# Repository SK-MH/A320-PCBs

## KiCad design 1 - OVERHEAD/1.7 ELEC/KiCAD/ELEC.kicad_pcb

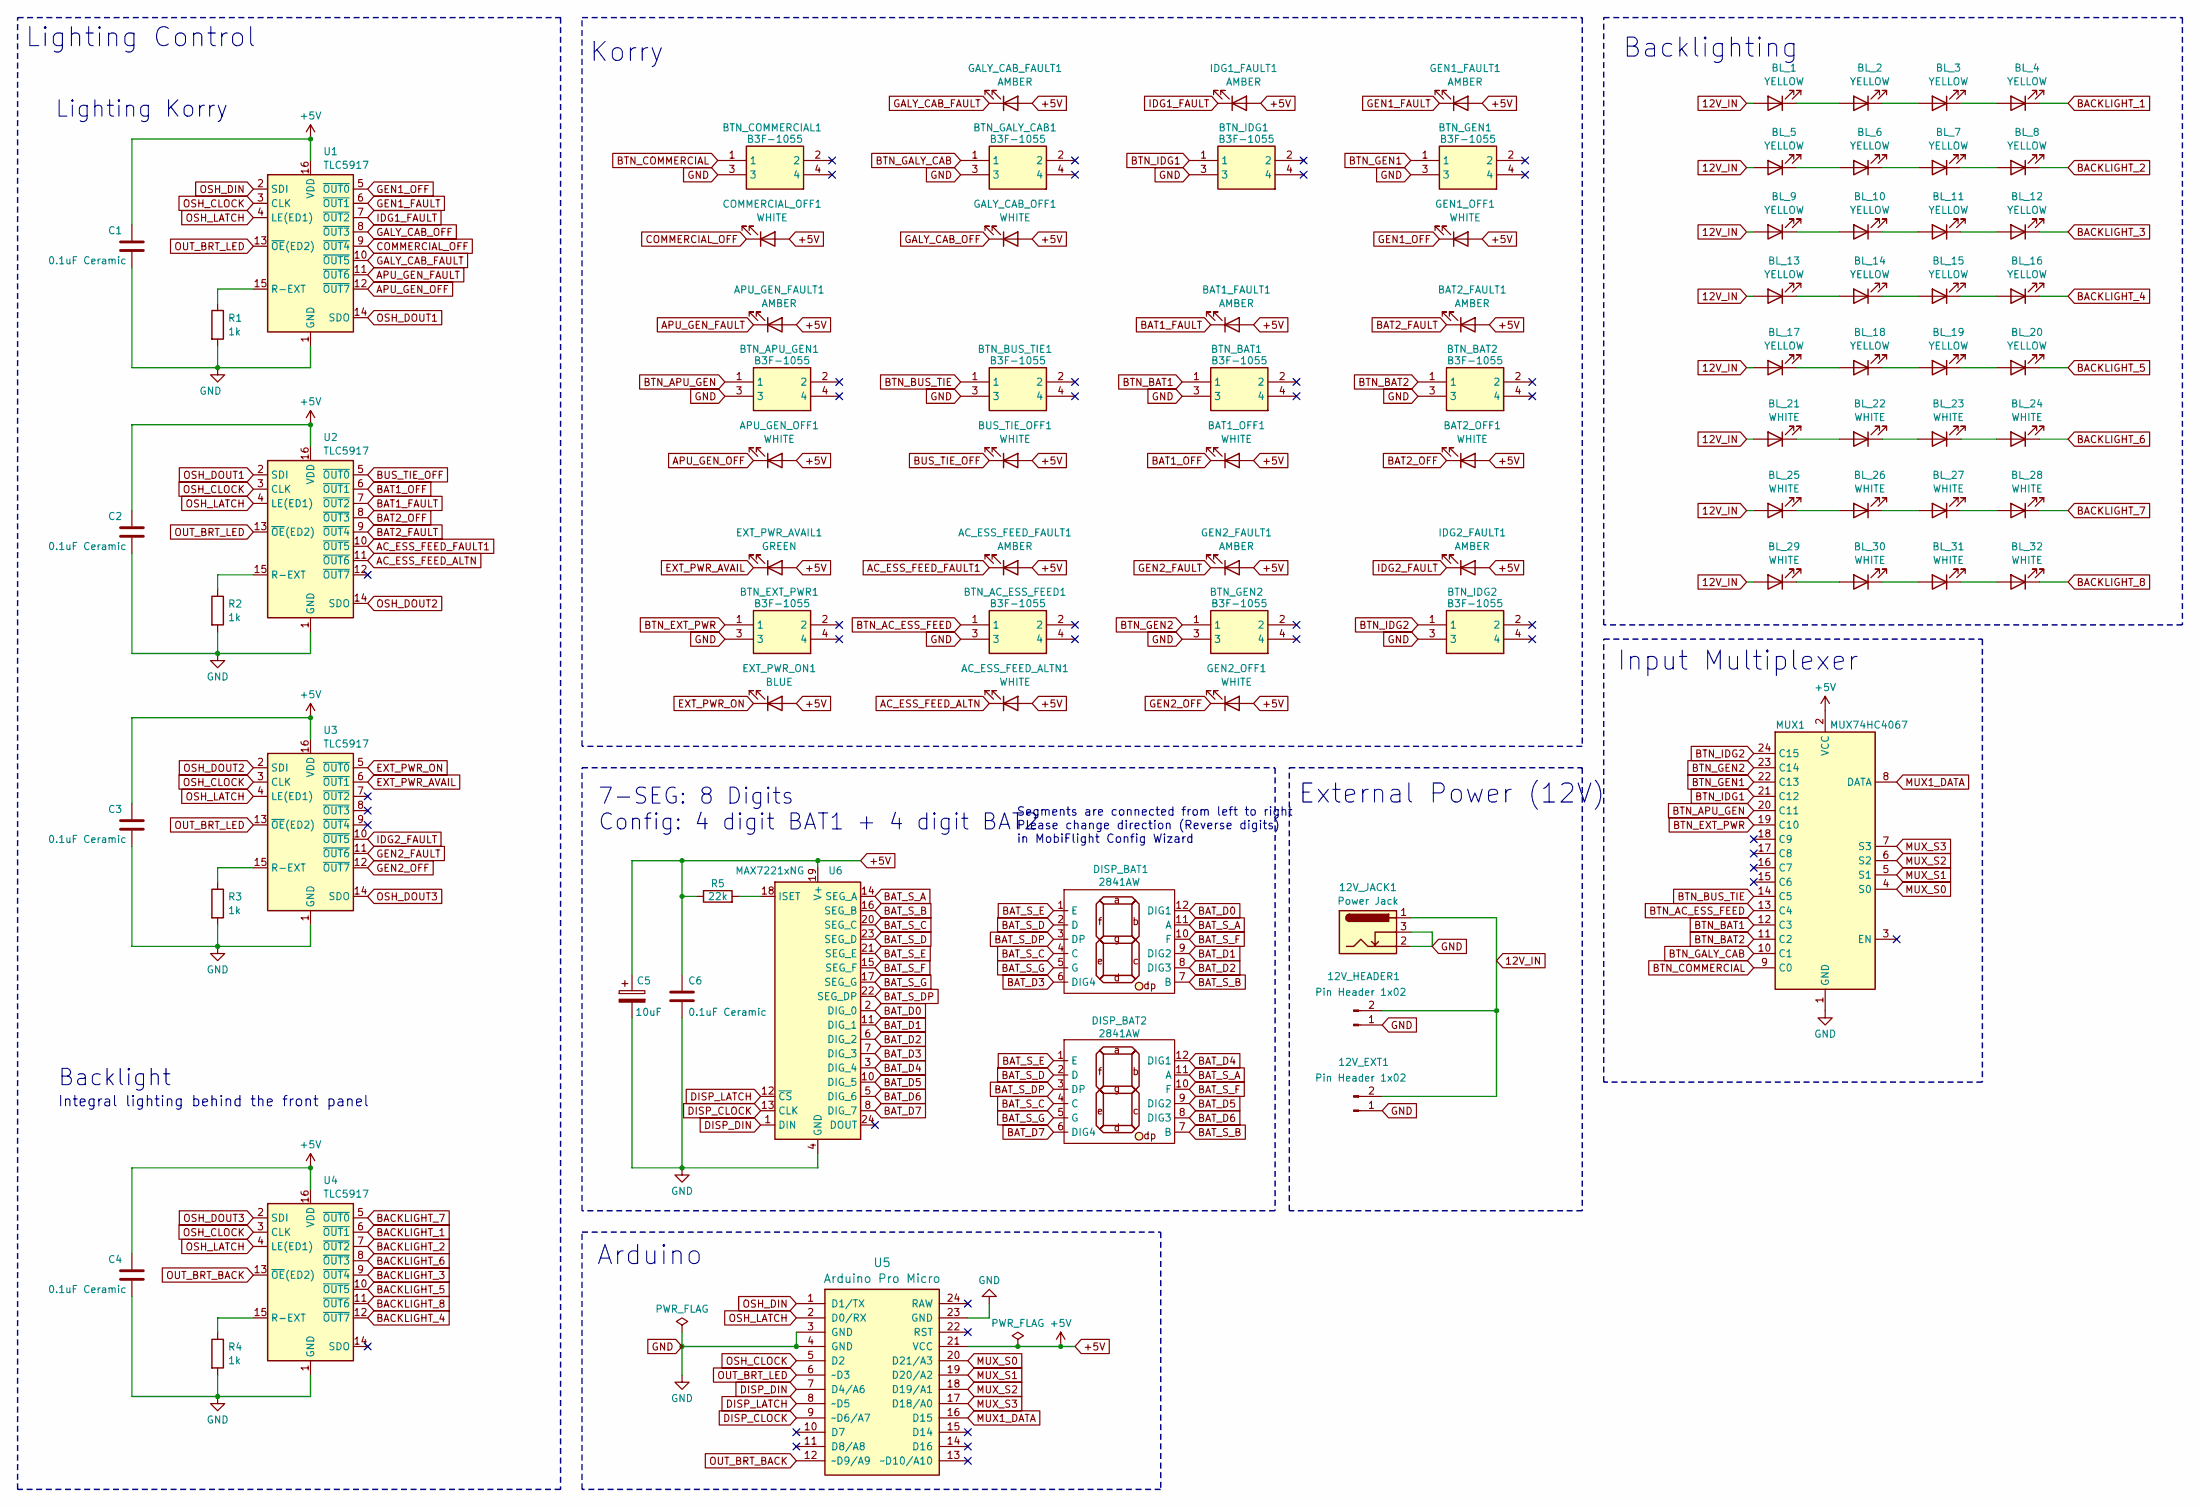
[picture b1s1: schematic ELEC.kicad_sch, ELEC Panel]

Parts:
12V_EXT1, 12V_HEADER1: Pin Header 1x02; JST_EH_B2B-EH-A_1x02_P2.50mm_Vertical
12V_JACK1: Power Jack; BarrelJack_Horizontal
AC_ESS_FEED_ALTN1: WHITE; LED_D3.0mm
AC_ESS_FEED_FAULT1: AMBER; LED_D3.0mm
APU_GEN_FAULT1: AMBER; LED_D3.0mm
APU_GEN_OFF1: WHITE; LED_D3.0mm
BAT1_FAULT1, BAT2_FAULT1: AMBER; LED_D3.0mm
BAT1_OFF1, BAT2_OFF1: WHITE; LED_D3.0mm
BL_1, BL_2, BL_3, BL_4, BL_5, BL_6, BL_7, BL_8, BL_9, BL_10, BL_11, BL_12, BL_13, BL_14, BL_15, BL_16, BL_17, BL_18, BL_19, BL_20: YELLOW; LED_D3.0mm
BL_21, BL_22, BL_23, BL_24, BL_25, BL_26, BL_27, BL_28, BL_29, BL_30, BL_31, BL_32: WHITE; LED_D3.0mm
BTN_AC_ESS_FEED1: B3F-1055; B3F1000; Mouser Part Number 653-B3F-1055
BTN_APU_GEN1: B3F-1055; B3F1000; Mouser Part Number 653-B3F-1055
BTN_BAT1, BTN_BAT2: B3F-1055; B3F1000; Mouser Part Number 653-B3F-1055
BTN_BUS_TIE1: B3F-1055; B3F1000; Mouser Part Number 653-B3F-1055
BTN_COMMERCIAL1: B3F-1055; B3F1000; Mouser Part Number 653-B3F-1055
BTN_EXT_PWR1: B3F-1055; B3F1000; Mouser Part Number 653-B3F-1055
BTN_GALY_CAB1: B3F-1055; B3F1000; Mouser Part Number 653-B3F-1055
BTN_GEN1, BTN_GEN2: B3F-1055; B3F1000; Mouser Part Number 653-B3F-1055
BTN_IDG1, BTN_IDG2: B3F-1055; B3F1000; Mouser Part Number 653-B3F-1055
BUS_TIE_OFF1: WHITE; LED_D3.0mm
C1, C2, C3, C4, C6: 0.1uF Ceramic; C_Disc_D3.0mm_W1.6mm_P2.50mm
C5: 10uF; CP_Radial_D4.0mm_P1.50mm
COMMERCIAL_OFF1: WHITE; LED_D3.0mm
DISP_BAT1, DISP_BAT2: 2841AW
EXT_PWR_AVAIL1: GREEN; LED_D3.0mm
EXT_PWR_ON1: BLUE; LED_D3.0mm
GALY_CAB_FAULT1: AMBER; LED_D3.0mm
GALY_CAB_OFF1: WHITE; LED_D3.0mm
GEN1_FAULT1, GEN2_FAULT1: AMBER; LED_D3.0mm
GEN1_OFF1, GEN2_OFF1: WHITE; LED_D3.0mm
IDG1_FAULT1, IDG2_FAULT1: AMBER; LED_D3.0mm
MUX1: MUX74HC4067
R1, R2, R3, R4: 1k; R_Axial_DIN0204_L3.6mm_D1.6mm_P7.62mm_Horizontal
R5: 22k; R_Axial_DIN0204_L3.6mm_D1.6mm_P7.62mm_Horizontal
U1, U2, U3, U4: TLC5917; DIP-16_W7.62mm
U5: Arduino Pro Micro; Sparkfun_Pro_Micro
U6: MAX7221xNG; DIP-24_W7.62mm

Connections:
12V_IN: 12V_EXT1.2, 12V_HEADER1.2, 12V_JACK1.1, BL_1.2 (A), BL_5.2 (A), BL_9.2 (A), BL_13.2 (A), BL_17.2 (A), BL_21.2 (A), BL_25.2 (A), BL_29.2 (A)
+5V: AC_ESS_FEED_ALTN1.2 (A), AC_ESS_FEED_FAULT1.2 (A), APU_GEN_FAULT1.2 (A), APU_GEN_OFF1.2 (A), BAT1_FAULT1.2 (A), BAT1_OFF1.2 (A), BAT2_FAULT1.2 (A), BAT2_OFF1.2 (A), BUS_TIE_OFF1.2 (A), C1.1, C2.1, C3.1, C4.1, C5.1, C6.1, COMMERCIAL_OFF1.2 (A), EXT_PWR_AVAIL1.2 (A), EXT_PWR_ON1.2 (A), GALY_CAB_FAULT1.2 (A), GALY_CAB_OFF1.2 (A), GEN1_FAULT1.2 (A), GEN1_OFF1.2 (A), GEN2_FAULT1.2 (A), GEN2_OFF1.2 (A), IDG1_FAULT1.2 (A), IDG2_FAULT1.2 (A), MUX1.2 (VCC), R5.1, U1.16 (VDD), U2.16 (VDD), U3.16 (VDD), U4.16 (VDD), U5.21 (VCC), U6.19 (V+)
AC_ESS_FEED_ALTN: AC_ESS_FEED_ALTN1.1 (K), U2.11 (~OUT6)
AC_ESS_FEED_FAULT1: AC_ESS_FEED_FAULT1.1 (K), U2.10 (~OUT5)
APU_GEN_FAULT: APU_GEN_FAULT1.1 (K), U1.11 (~OUT6)
APU_GEN_OFF: APU_GEN_OFF1.1 (K), U1.12 (~OUT7)
BACKLIGHT_1: BL_4.1 (K), U4.6 (~OUT1)
BACKLIGHT_2: BL_8.1 (K), U4.7 (~OUT2)
BACKLIGHT_3: BL_12.1 (K), U4.9 (~OUT4)
BACKLIGHT_4: BL_16.1 (K), U4.12 (~OUT7)
BACKLIGHT_5: BL_20.1 (K), U4.10 (~OUT5)
BACKLIGHT_6: BL_24.1 (K), U4.8 (~OUT3)
BACKLIGHT_7: BL_28.1 (K), U4.5 (~OUT0)
BACKLIGHT_8: BL_32.1 (K), U4.11 (~OUT6)
BAT1_FAULT: BAT1_FAULT1.1 (K), U2.7 (~OUT2)
BAT1_OFF: BAT1_OFF1.1 (K), U2.6 (~OUT1)
BAT2_FAULT: BAT2_FAULT1.1 (K), U2.9 (~OUT4)
BAT2_OFF: BAT2_OFF1.1 (K), U2.8 (~OUT3)
BAT_D0: DISP_BAT1.12 (DIG1), U6.2 (DIG_0)
BAT_D1: DISP_BAT1.9 (DIG2), U6.11 (DIG_1)
BAT_D2: DISP_BAT1.8 (DIG3), U6.6 (DIG_2)
BAT_D3: DISP_BAT1.6 (DIG4), U6.7 (DIG_3)
BAT_D4: DISP_BAT2.12 (DIG1), U6.3 (DIG_4)
BAT_D5: DISP_BAT2.9 (DIG2), U6.10 (DIG_5)
BAT_D6: DISP_BAT2.8 (DIG3), U6.5 (DIG_6)
BAT_D7: DISP_BAT2.6 (DIG4), U6.8 (DIG_7)
BAT_S_A: DISP_BAT1.11 (A), DISP_BAT2.11 (A), U6.14 (SEG_A)
BAT_S_B: DISP_BAT1.7 (B), DISP_BAT2.7 (B), U6.16 (SEG_B)
BAT_S_C: DISP_BAT1.4 (C), DISP_BAT2.4 (C), U6.20 (SEG_C)
BAT_S_D: DISP_BAT1.2 (D), DISP_BAT2.2 (D), U6.23 (SEG_D)
BAT_S_DP: DISP_BAT1.3 (DP), DISP_BAT2.3 (DP), U6.22 (SEG_DP)
BAT_S_E: DISP_BAT1.1 (E), DISP_BAT2.1 (E), U6.21 (SEG_E)
BAT_S_F: DISP_BAT1.10 (F), DISP_BAT2.10 (F), U6.15 (SEG_F)
BAT_S_G: DISP_BAT1.5 (G), DISP_BAT2.5 (G), U6.17 (SEG_G)
BTN_AC_ESS_FEED: BTN_AC_ESS_FEED1.1, MUX1.13 (C4)
BTN_APU_GEN: BTN_APU_GEN1.1, MUX1.20 (C11)
BTN_BAT1: BTN_BAT1.1, MUX1.12 (C3)
BTN_BAT2: BTN_BAT2.1, MUX1.11 (C2)
BTN_BUS_TIE: BTN_BUS_TIE1.1, MUX1.14 (C5)
BTN_COMMERCIAL: BTN_COMMERCIAL1.1, MUX1.9 (C0)
BTN_EXT_PWR: BTN_EXT_PWR1.1, MUX1.19 (C10)
BTN_GALY_CAB: BTN_GALY_CAB1.1, MUX1.10 (C1)
BTN_GEN1: BTN_GEN1.1, MUX1.22 (C13)
BTN_GEN2: BTN_GEN2.1, MUX1.23 (C14)
BTN_IDG1: BTN_IDG1.1, MUX1.21 (C12)
BTN_IDG2: BTN_IDG2.1, MUX1.24 (C15)
BUS_TIE_OFF: BUS_TIE_OFF1.1 (K), U2.5 (~OUT0)
COMMERCIAL_OFF: COMMERCIAL_OFF1.1 (K), U1.9 (~OUT4)
DISP_CLOCK: U5.9 (~D6/A7), U6.13 (CLK)
DISP_DIN: U5.7 (D4/A6), U6.1 (DIN)
DISP_LATCH: U5.8 (~D5), U6.12 (~CS)
EXT_PWR_AVAIL: EXT_PWR_AVAIL1.1 (K), U3.6 (~OUT1)
EXT_PWR_ON: EXT_PWR_ON1.1 (K), U3.5 (~OUT0)
GALY_CAB_FAULT: GALY_CAB_FAULT1.1 (K), U1.10 (~OUT5)
GALY_CAB_OFF: GALY_CAB_OFF1.1 (K), U1.8 (~OUT3)
GEN1_FAULT: GEN1_FAULT1.1 (K), U1.6 (~OUT1)
GEN1_OFF: GEN1_OFF1.1 (K), U1.5 (~OUT0)
GEN2_FAULT: GEN2_FAULT1.1 (K), U3.11 (~OUT6)
GEN2_OFF: GEN2_OFF1.1 (K), U3.12 (~OUT7)
GND: 12V_EXT1.1, 12V_HEADER1.1, 12V_JACK1.2, 12V_JACK1.3, BTN_AC_ESS_FEED1.3, BTN_APU_GEN1.3, BTN_BAT1.3, BTN_BAT2.3, BTN_BUS_TIE1.3, BTN_COMMERCIAL1.3, BTN_EXT_PWR1.3, BTN_GALY_CAB1.3, BTN_GEN1.3, BTN_GEN2.3, BTN_IDG1.3, BTN_IDG2.3, C1.2, C2.2, C3.2, C4.2, C5.2, C6.2, MUX1.1 (GND), R1.2, R2.2, R3.2, R4.2, U1.1 (GND), U2.1 (GND), U3.1 (GND), U4.1 (GND), U5.3 (GND), U5.4 (GND), U5.23 (GND), U6.4 (GND), U6.9 (GND)
IDG1_FAULT: IDG1_FAULT1.1 (K), U1.7 (~OUT2)
IDG2_FAULT: IDG2_FAULT1.1 (K), U3.10 (~OUT5)
MUX1_DATA: MUX1.8 (DATA), U5.16 (D15)
MUX_S0: MUX1.4 (S0), U5.20 (D21/A3)
MUX_S1: MUX1.5 (S1), U5.19 (D20/A2)
MUX_S2: MUX1.6 (S2), U5.18 (D19/A1)
MUX_S3: MUX1.7 (S3), U5.17 (D18/A0)
unnamed: BL_1.1 (K), BL_2.2 (A)
unnamed: BL_2.1 (K), BL_3.2 (A)
unnamed: BL_3.1 (K), BL_4.2 (A)
unnamed: BL_5.1 (K), BL_6.2 (A)
unnamed: BL_6.1 (K), BL_7.2 (A)
unnamed: BL_7.1 (K), BL_8.2 (A)
unnamed: BL_9.1 (K), BL_10.2 (A)
unnamed: BL_10.1 (K), BL_11.2 (A)
unnamed: BL_11.1 (K), BL_12.2 (A)
unnamed: BL_13.1 (K), BL_14.2 (A)
unnamed: BL_14.1 (K), BL_15.2 (A)
unnamed: BL_15.1 (K), BL_16.2 (A)
unnamed: BL_17.1 (K), BL_18.2 (A)
unnamed: BL_18.1 (K), BL_19.2 (A)
unnamed: BL_19.1 (K), BL_20.2 (A)
unnamed: BL_21.1 (K), BL_22.2 (A)
unnamed: BL_22.1 (K), BL_23.2 (A)
unnamed: BL_23.1 (K), BL_24.2 (A)
unnamed: BL_25.1 (K), BL_26.2 (A)
unnamed: BL_26.1 (K), BL_27.2 (A)
unnamed: BL_27.1 (K), BL_28.2 (A)
unnamed: BL_29.1 (K), BL_30.2 (A)
unnamed: BL_30.1 (K), BL_31.2 (A)
unnamed: BL_31.1 (K), BL_32.2 (A)
unnamed: R1.1, U1.15 (R-EXT)
unnamed: R2.1, U2.15 (R-EXT)
unnamed: R3.1, U3.15 (R-EXT)
unnamed: R4.1, U4.15 (R-EXT)
unnamed: R5.2, U6.18 (ISET)
OSH_CLOCK: U1.3 (CLK), U2.3 (CLK), U3.3 (CLK), U4.3 (CLK), U5.5 (D2)
OSH_DIN: U1.2 (SDI), U5.1 (D1/TX)
OSH_DOUT1: U1.14 (SDO), U2.2 (SDI)
OSH_DOUT2: U2.14 (SDO), U3.2 (SDI)
OSH_DOUT3: U3.14 (SDO), U4.2 (SDI)
OSH_LATCH: U1.4 (LE(ED1)), U2.4 (LE(ED1)), U3.4 (LE(ED1)), U4.4 (LE(ED1)), U5.2 (D0/RX)
OUT_BRT_BACK: U4.13 (~OE(ED2)), U5.12 (~D9/A9)
OUT_BRT_LED: U1.13 (~OE(ED2)), U2.13 (~OE(ED2)), U3.13 (~OE(ED2)), U5.6 (~D3)

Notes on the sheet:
Backlighting
7-SEG: 8 Digits Config: 4 digit BAT1 + 4 digit BAT2
Arduino
Korry
Segments are connected from left to right Please change direction (Reverse digits) in MobiFlight Config Wizard
Input Multiplexer
External Power (12V)
Lighting Korry
Lighting Control
Integral lighting behind the front panel
Backlight

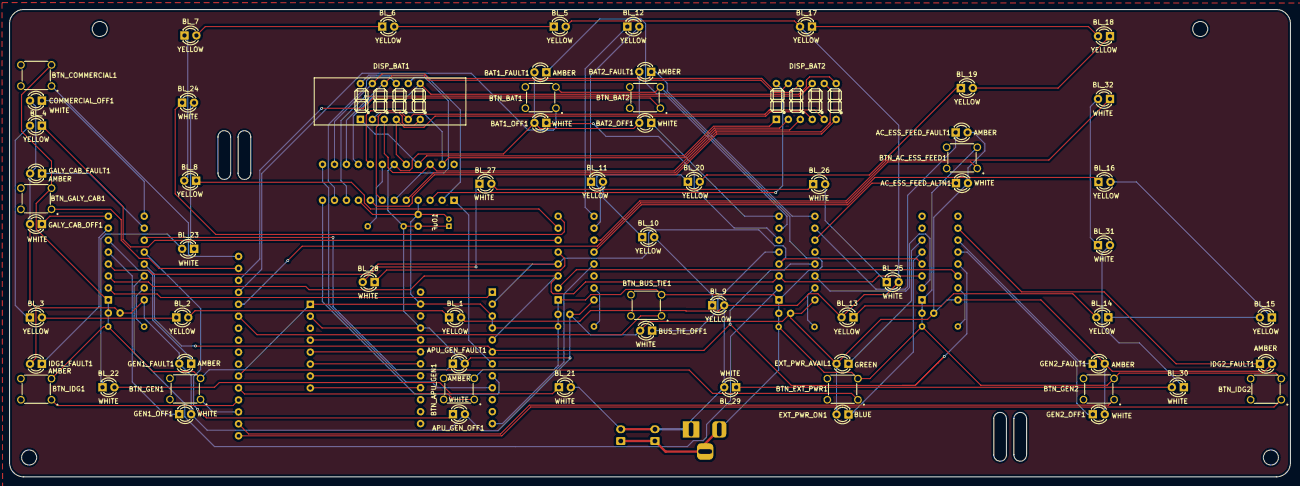
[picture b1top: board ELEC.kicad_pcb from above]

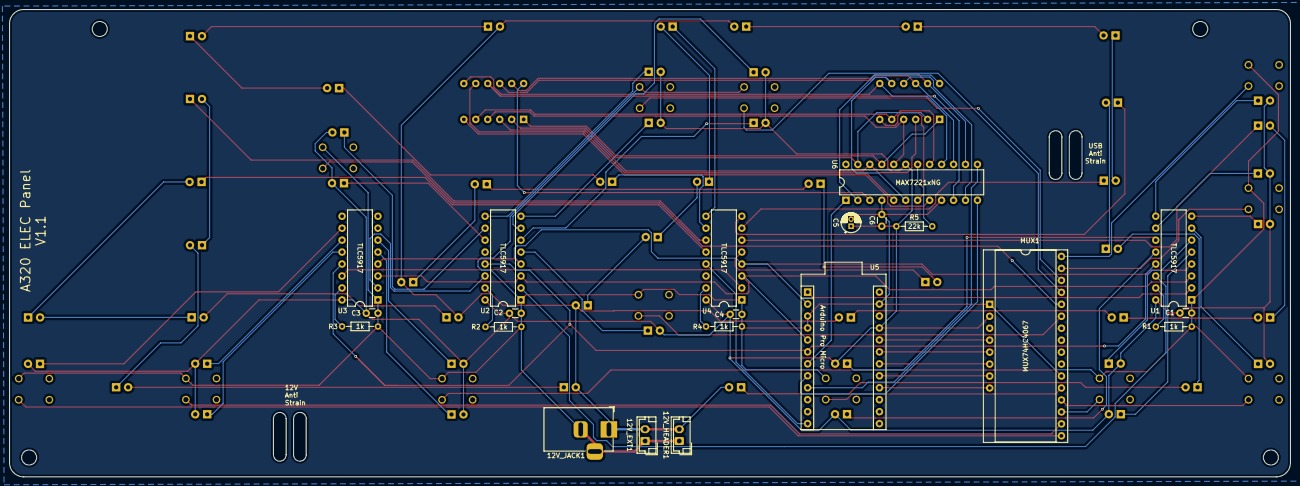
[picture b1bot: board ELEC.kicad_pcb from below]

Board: 2 copper layers, 272.1 x 99.3 mm, 87 parts (21 on the bottom side), 104 nets.

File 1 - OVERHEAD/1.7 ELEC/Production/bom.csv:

Designator,Footprint,Quantity,Value,LCSC Part #
"12V_EXT1, 12V_HEADER1",JST_EH_B2B-EH-A_1x02_P2.50mm_Vertical,2,Pin Header 1x02,
12V_JACK1,BarrelJack_Horizontal,1,Power Jack,
"AC_ESS_FEED_ALTN1, APU_GEN_OFF1, BAT1_OFF1, BAT2_OFF1, BL_21, BL_22, BL_23, BL_24, BL_25, BL_26, BL_27, BL_28, BL_29, BL_30, BL_31, BL_32, BUS_TIE_OFF1, COMMERCIAL_OFF1, GALY_CAB_OFF1, GEN1_OFF1, GEN2_OFF1",LED_D3.0mm,21,WHITE,
"AC_ESS_FEED_FAULT1, APU_GEN_FAULT1, BAT1_FAULT1, BAT2_FAULT1, GALY_CAB_FAULT1, GEN1_FAULT1, GEN2_FAULT1, IDG1_FAULT1, IDG2_FAULT1",LED_D3.0mm,9,AMBER,
"BL_1, BL_10, BL_11, BL_12, BL_13, BL_14, BL_15, BL_16, BL_17, BL_18, BL_19, BL_2, BL_20, BL_3, BL_4, BL_5, BL_6, BL_7, BL_8, BL_9",LED_D3.0mm,20,YELLOW,
"BTN_AC_ESS_FEED1, BTN_APU_GEN1, BTN_BAT1, BTN_BAT2, BTN_BUS_TIE1, BTN_COMMERCIAL1, BTN_EXT_PWR1, BTN_GALY_CAB1, BTN_GEN1, BTN_GEN2, BTN_IDG1, BTN_IDG2",B3F1000,12,B3F-1055,
"C1, C2, C3, C4, C6",C_Disc_D3.0mm_W1.6mm_P2.50mm,5,0.1uF Ceramic,
C5,CP_Radial_D4.0mm_P1.50mm,1,10uF,
"DISP_BAT1, DISP_BAT2",2841AW,2,2841AW,
EXT_PWR_AVAIL1,LED_D3.0mm,1,GREEN,
EXT_PWR_ON1,LED_D3.0mm,1,BLUE,
MUX1,MUX74HC4067,1,MUX74HC4067,
"R1, R2, R3, R4",R_Axial_DIN0204_L3.6mm_D1.6mm_P7.62mm_Horizontal,4,1k,
R5,R_Axial_DIN0204_L3.6mm_D1.6mm_P7.62mm_Horizontal,1,22k,
"U1, U2, U3, U4",DIP-16_W7.62mm,4,TLC5917,
U5,Sparkfun_Pro_Micro,1,Arduino Pro Micro,
U6,DIP-24_W7.62mm,1,MAX7221xNG,

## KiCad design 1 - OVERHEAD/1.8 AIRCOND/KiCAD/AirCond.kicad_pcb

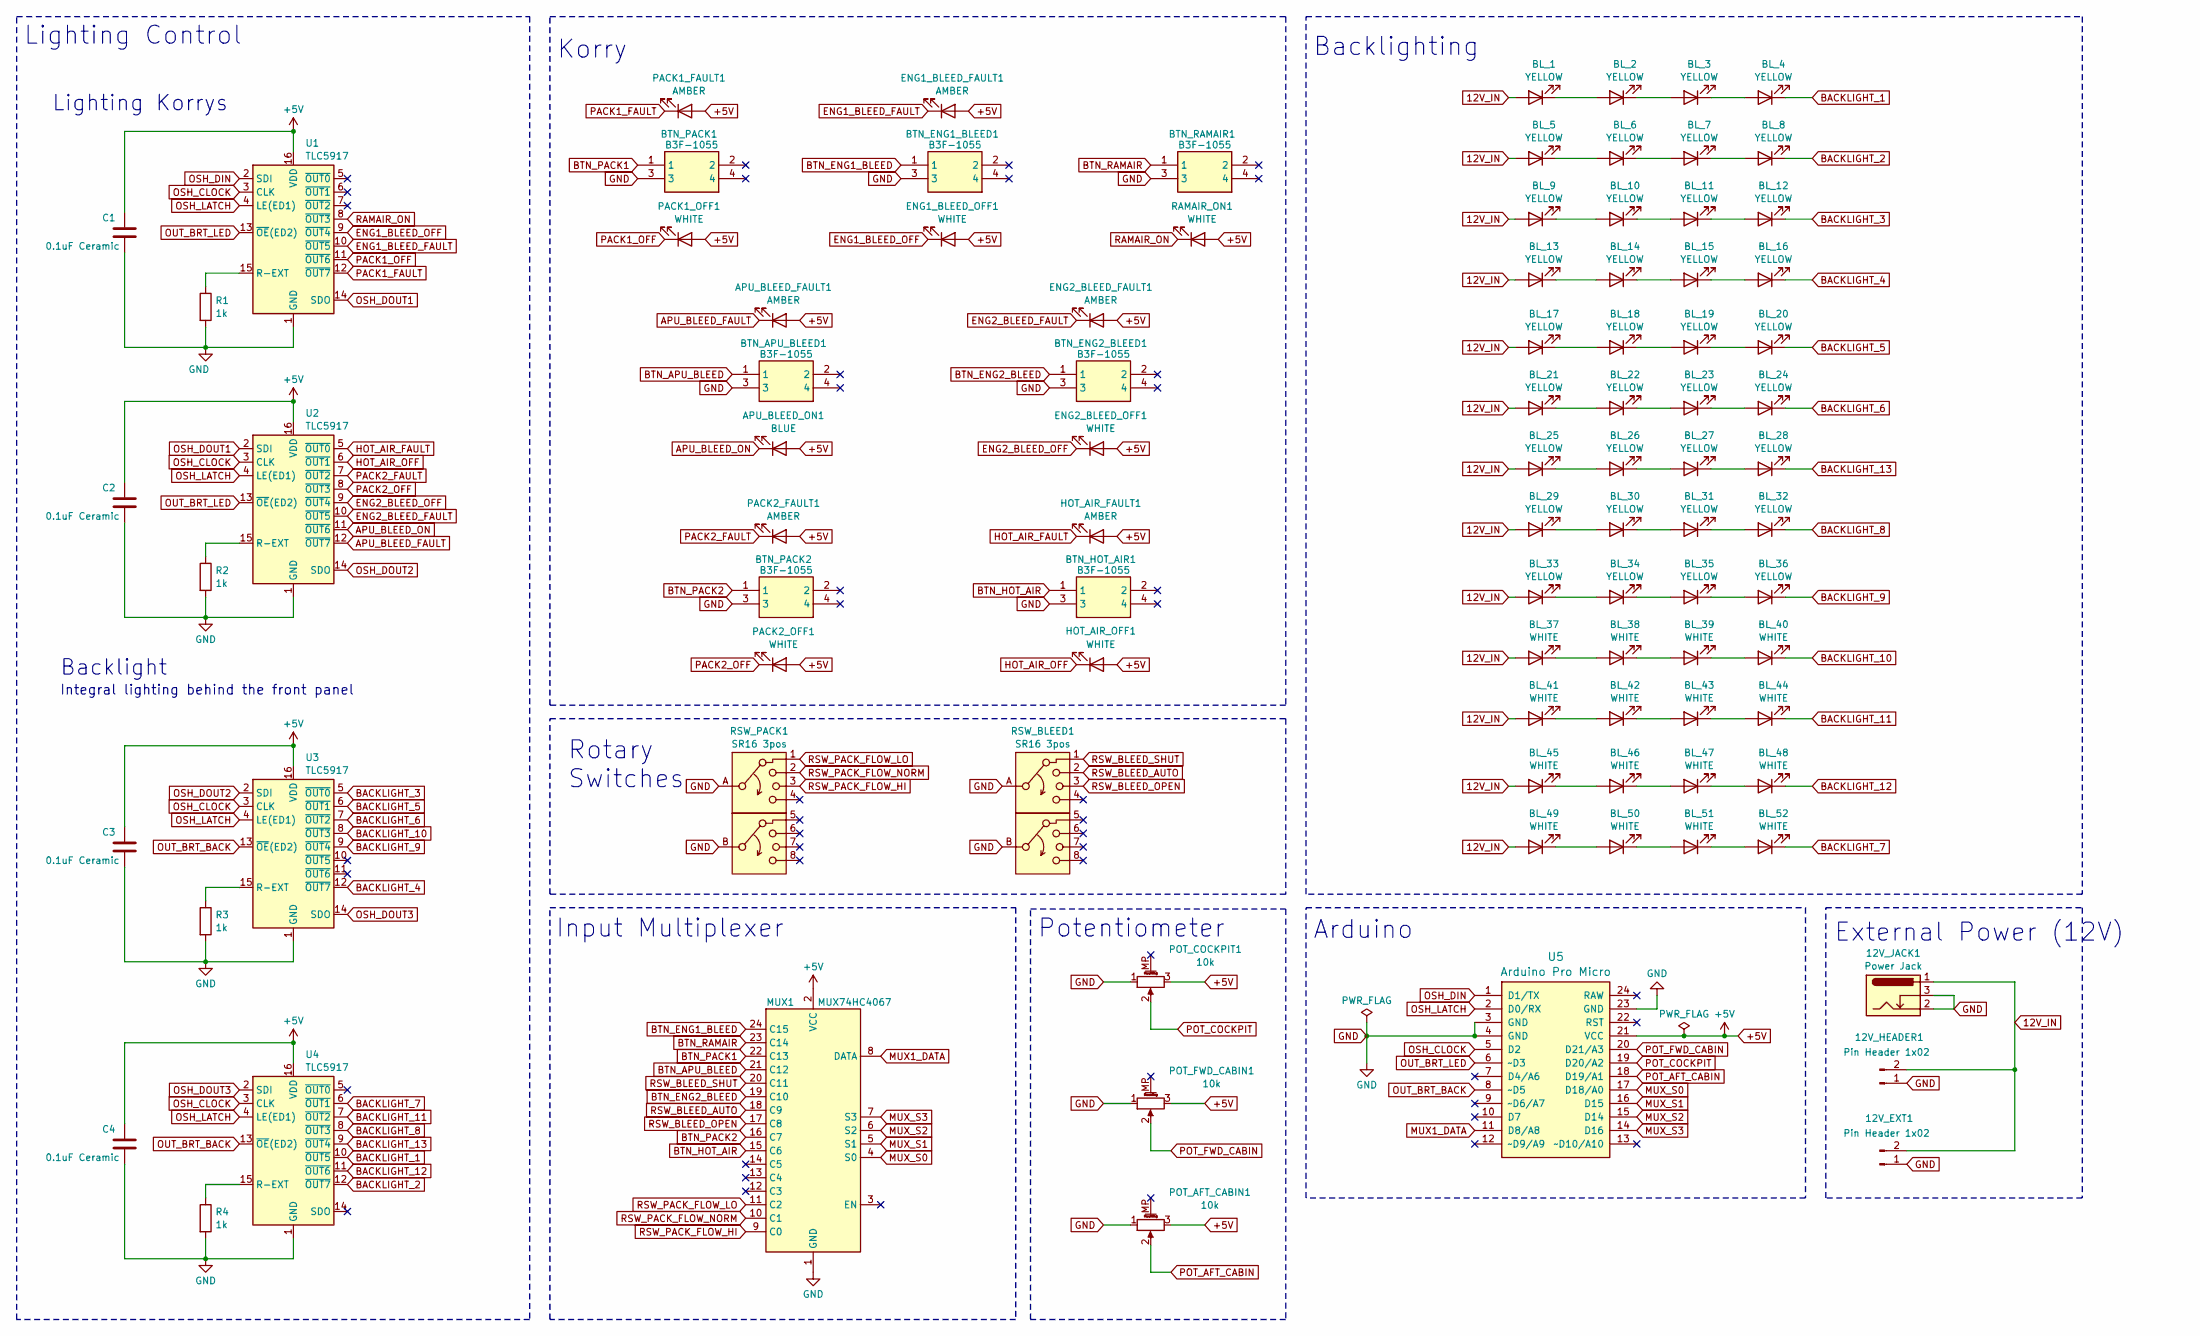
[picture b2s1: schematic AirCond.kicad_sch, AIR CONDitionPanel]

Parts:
12V_EXT1, 12V_HEADER1: Pin Header 1x02; JST_EH_B2B-EH-A_1x02_P2.50mm_Vertical
12V_JACK1: Power Jack; BarrelJack_Horizontal
APU_BLEED_FAULT1: AMBER; LED_D3.0mm
APU_BLEED_ON1: BLUE; LED_D3.0mm
BL_1, BL_2, BL_3, BL_4, BL_5, BL_6, BL_7, BL_8, BL_9, BL_10, BL_11, BL_12, BL_13, BL_14, BL_15, BL_16, BL_17, BL_18, BL_19, BL_20, BL_21, BL_22, BL_23, BL_24, BL_25, BL_26, BL_27, BL_28, BL_29, BL_30, BL_31, BL_32, BL_33, BL_34, BL_35, BL_36: YELLOW; LED_D3.0mm
BL_37, BL_38, BL_39, BL_40, BL_41, BL_42, BL_43, BL_44, BL_45, BL_46, BL_47, BL_48, BL_49, BL_50, BL_51, BL_52: WHITE; LED_D3.0mm
BTN_APU_BLEED1: B3F-1055; B3F1000; Mouser Part Number 653-B3F-1055
BTN_ENG1_BLEED1, BTN_ENG2_BLEED1: B3F-1055; B3F1000; Mouser Part Number 653-B3F-1055
BTN_HOT_AIR1: B3F-1055; B3F1000; Mouser Part Number 653-B3F-1055
BTN_PACK1, BTN_PACK2: B3F-1055; B3F1000; Mouser Part Number 653-B3F-1055
BTN_RAMAIR1: B3F-1055; B3F1000; Mouser Part Number 653-B3F-1055
C1, C2, C3, C4: 0.1uF Ceramic; C_Disc_D3.0mm_W1.6mm_P2.50mm
ENG1_BLEED_FAULT1, ENG2_BLEED_FAULT1: AMBER; LED_D3.0mm
ENG1_BLEED_OFF1, ENG2_BLEED_OFF1: WHITE; LED_D3.0mm
HOT_AIR_FAULT1: AMBER; LED_D3.0mm
HOT_AIR_OFF1: WHITE; LED_D3.0mm
MUX1: MUX74HC4067
PACK1_FAULT1, PACK2_FAULT1: AMBER; LED_D3.0mm
PACK1_OFF1, PACK2_OFF1: WHITE; LED_D3.0mm
POT_AFT_CABIN1: 10k; Potentiometer_Alps_RK09K_Single_Vertical
POT_COCKPIT1: 10k; Potentiometer_Alps_RK09K_Single_Vertical
POT_FWD_CABIN1: 10k; Potentiometer_Alps_RK09K_Single_Vertical
R1, R2, R3, R4: 1k; R_Axial_DIN0204_L3.6mm_D1.6mm_P7.62mm_Horizontal
RAMAIR_ON1: WHITE; LED_D3.0mm
RSW_BLEED1: SR16 3pos; SR16-AB
RSW_PACK1: SR16 3pos; SR16-AB
U1, U2, U3, U4: TLC5917; DIP-16_W7.62mm
U5: Arduino Pro Micro; Sparkfun_Pro_Micro

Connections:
12V_IN: 12V_EXT1.2, 12V_HEADER1.2, 12V_JACK1.1, BL_1.2 (A), BL_5.2 (A), BL_9.2 (A), BL_13.2 (A), BL_17.2 (A), BL_21.2 (A), BL_25.2 (A), BL_29.2 (A), BL_33.2 (A), BL_37.2 (A), BL_41.2 (A), BL_45.2 (A), BL_49.2 (A)
+5V: APU_BLEED_FAULT1.2 (A), APU_BLEED_ON1.2 (A), C1.1, C2.1, C3.1, C4.1, ENG1_BLEED_FAULT1.2 (A), ENG1_BLEED_OFF1.2 (A), ENG2_BLEED_FAULT1.2 (A), ENG2_BLEED_OFF1.2 (A), HOT_AIR_FAULT1.2 (A), HOT_AIR_OFF1.2 (A), MUX1.2 (VCC), PACK1_FAULT1.2 (A), PACK1_OFF1.2 (A), PACK2_FAULT1.2 (A), PACK2_OFF1.2 (A), POT_AFT_CABIN1.3, POT_COCKPIT1.3, POT_FWD_CABIN1.3, RAMAIR_ON1.2 (A), U1.16 (VDD), U2.16 (VDD), U3.16 (VDD), U4.16 (VDD), U5.21 (VCC)
APU_BLEED_FAULT: APU_BLEED_FAULT1.1 (K), U2.12 (~OUT7)
APU_BLEED_ON: APU_BLEED_ON1.1 (K), U2.11 (~OUT6)
BACKLIGHT_1: BL_4.1 (K), U4.10 (~OUT5)
BACKLIGHT_2: BL_8.1 (K), U4.12 (~OUT7)
BACKLIGHT_3: BL_12.1 (K), U3.5 (~OUT0)
BACKLIGHT_4: BL_16.1 (K), U3.12 (~OUT7)
BACKLIGHT_5: BL_20.1 (K), U3.6 (~OUT1)
BACKLIGHT_6: BL_24.1 (K), U3.7 (~OUT2)
BACKLIGHT_7: BL_52.1 (K), U4.6 (~OUT1)
BACKLIGHT_8: BL_32.1 (K), U4.8 (~OUT3)
BACKLIGHT_9: BL_36.1 (K), U3.9 (~OUT4)
BACKLIGHT_10: BL_40.1 (K), U3.8 (~OUT3)
BACKLIGHT_11: BL_44.1 (K), U4.7 (~OUT2)
BACKLIGHT_12: BL_48.1 (K), U4.11 (~OUT6)
BACKLIGHT_13: BL_28.1 (K), U4.9 (~OUT4)
BTN_APU_BLEED: BTN_APU_BLEED1.1, MUX1.21 (C12)
BTN_ENG1_BLEED: BTN_ENG1_BLEED1.1, MUX1.24 (C15)
BTN_ENG2_BLEED: BTN_ENG2_BLEED1.1, MUX1.19 (C10)
BTN_HOT_AIR: BTN_HOT_AIR1.1, MUX1.15 (C6)
BTN_PACK1: BTN_PACK1.1, MUX1.22 (C13)
BTN_PACK2: BTN_PACK2.1, MUX1.16 (C7)
BTN_RAMAIR: BTN_RAMAIR1.1, MUX1.23 (C14)
ENG1_BLEED_FAULT: ENG1_BLEED_FAULT1.1 (K), U1.10 (~OUT5)
ENG1_BLEED_OFF: ENG1_BLEED_OFF1.1 (K), U1.9 (~OUT4)
ENG2_BLEED_FAULT: ENG2_BLEED_FAULT1.1 (K), U2.10 (~OUT5)
ENG2_BLEED_OFF: ENG2_BLEED_OFF1.1 (K), U2.9 (~OUT4)
GND: 12V_EXT1.1, 12V_HEADER1.1, 12V_JACK1.2, 12V_JACK1.3, BTN_APU_BLEED1.3, BTN_ENG1_BLEED1.3, BTN_ENG2_BLEED1.3, BTN_HOT_AIR1.3, BTN_PACK1.3, BTN_PACK2.3, BTN_RAMAIR1.3, C1.2, C2.2, C3.2, C4.2, MUX1.1 (GND), POT_AFT_CABIN1.1, POT_COCKPIT1.1, POT_FWD_CABIN1.1, R1.2, R2.2, R3.2, R4.2, RSW_BLEED1.A, RSW_BLEED1.B, RSW_PACK1.A, RSW_PACK1.B, U1.1 (GND), U2.1 (GND), U3.1 (GND), U4.1 (GND), U5.3 (GND), U5.4 (GND), U5.23 (GND)
HOT_AIR_FAULT: HOT_AIR_FAULT1.1 (K), U2.5 (~OUT0)
HOT_AIR_OFF: HOT_AIR_OFF1.1 (K), U2.6 (~OUT1)
MUX1_DATA: MUX1.8 (DATA), U5.11 (D8/A8)
MUX_S0: MUX1.4 (S0), U5.17 (D18/A0)
MUX_S1: MUX1.5 (S1), U5.16 (D15)
MUX_S2: MUX1.6 (S2), U5.15 (D14)
MUX_S3: MUX1.7 (S3), U5.14 (D16)
unnamed: BL_1.1 (K), BL_2.2 (A)
unnamed: BL_2.1 (K), BL_3.2 (A)
unnamed: BL_3.1 (K), BL_4.2 (A)
unnamed: BL_5.1 (K), BL_6.2 (A)
unnamed: BL_6.1 (K), BL_7.2 (A)
unnamed: BL_7.1 (K), BL_8.2 (A)
unnamed: BL_9.1 (K), BL_10.2 (A)
unnamed: BL_10.1 (K), BL_11.2 (A)
unnamed: BL_11.1 (K), BL_12.2 (A)
unnamed: BL_13.1 (K), BL_14.2 (A)
unnamed: BL_14.1 (K), BL_15.2 (A)
unnamed: BL_15.1 (K), BL_16.2 (A)
unnamed: BL_17.1 (K), BL_18.2 (A)
unnamed: BL_18.1 (K), BL_19.2 (A)
unnamed: BL_19.1 (K), BL_20.2 (A)
unnamed: BL_21.1 (K), BL_22.2 (A)
unnamed: BL_22.1 (K), BL_23.2 (A)
unnamed: BL_23.1 (K), BL_24.2 (A)
unnamed: BL_25.1 (K), BL_26.2 (A)
unnamed: BL_26.1 (K), BL_27.2 (A)
unnamed: BL_27.1 (K), BL_28.2 (A)
unnamed: BL_29.1 (K), BL_30.2 (A)
unnamed: BL_30.1 (K), BL_31.2 (A)
unnamed: BL_31.1 (K), BL_32.2 (A)
unnamed: BL_33.1 (K), BL_34.2 (A)
unnamed: BL_34.1 (K), BL_35.2 (A)
unnamed: BL_35.1 (K), BL_36.2 (A)
unnamed: BL_37.1 (K), BL_38.2 (A)
unnamed: BL_38.1 (K), BL_39.2 (A)
unnamed: BL_39.1 (K), BL_40.2 (A)
unnamed: BL_41.1 (K), BL_42.2 (A)
unnamed: BL_42.1 (K), BL_43.2 (A)
unnamed: BL_43.1 (K), BL_44.2 (A)
unnamed: BL_45.1 (K), BL_46.2 (A)
unnamed: BL_46.1 (K), BL_47.2 (A)
unnamed: BL_47.1 (K), BL_48.2 (A)
unnamed: BL_49.1 (K), BL_50.2 (A)
unnamed: BL_50.1 (K), BL_51.2 (A)
unnamed: BL_51.1 (K), BL_52.2 (A)
unnamed: R1.1, U1.15 (R-EXT)
unnamed: R2.1, U2.15 (R-EXT)
unnamed: R3.1, U3.15 (R-EXT)
unnamed: R4.1, U4.15 (R-EXT)
OSH_CLOCK: U1.3 (CLK), U2.3 (CLK), U3.3 (CLK), U4.3 (CLK), U5.5 (D2)
OSH_DIN: U1.2 (SDI), U5.1 (D1/TX)
OSH_DOUT1: U1.14 (SDO), U2.2 (SDI)
OSH_DOUT2: U2.14 (SDO), U3.2 (SDI)
OSH_DOUT3: U3.14 (SDO), U4.2 (SDI)
OSH_LATCH: U1.4 (LE(ED1)), U2.4 (LE(ED1)), U3.4 (LE(ED1)), U4.4 (LE(ED1)), U5.2 (D0/RX)
OUT_BRT_BACK: U3.13 (~OE(ED2)), U4.13 (~OE(ED2)), U5.8 (~D5)
OUT_BRT_LED: U1.13 (~OE(ED2)), U2.13 (~OE(ED2)), U5.6 (~D3)
PACK1_FAULT: PACK1_FAULT1.1 (K), U1.12 (~OUT7)
PACK1_OFF: PACK1_OFF1.1 (K), U1.11 (~OUT6)
PACK2_FAULT: PACK2_FAULT1.1 (K), U2.7 (~OUT2)
PACK2_OFF: PACK2_OFF1.1 (K), U2.8 (~OUT3)
POT_AFT_CABIN: POT_AFT_CABIN1.2, U5.18 (D19/A1)
POT_COCKPIT: POT_COCKPIT1.2, U5.19 (D20/A2)
POT_FWD_CABIN: POT_FWD_CABIN1.2, U5.20 (D21/A3)
RAMAIR_ON: RAMAIR_ON1.1 (K), U1.8 (~OUT3)
RSW_BLEED_AUTO: MUX1.18 (C9), RSW_BLEED1.2
RSW_BLEED_OPEN: MUX1.17 (C8), RSW_BLEED1.3
RSW_BLEED_SHUT: MUX1.20 (C11), RSW_BLEED1.1
RSW_PACK_FLOW_HI: MUX1.9 (C0), RSW_PACK1.3
RSW_PACK_FLOW_LO: MUX1.11 (C2), RSW_PACK1.1
RSW_PACK_FLOW_NORM: MUX1.10 (C1), RSW_PACK1.2

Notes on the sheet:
Backlighting
Arduino
Rotary Switches
Korry
Potentiometer
Input Multiplexer
External Power (12V)
Lighting Korrys
Lighting Control
Integral lighting behind the front panel
Backlight

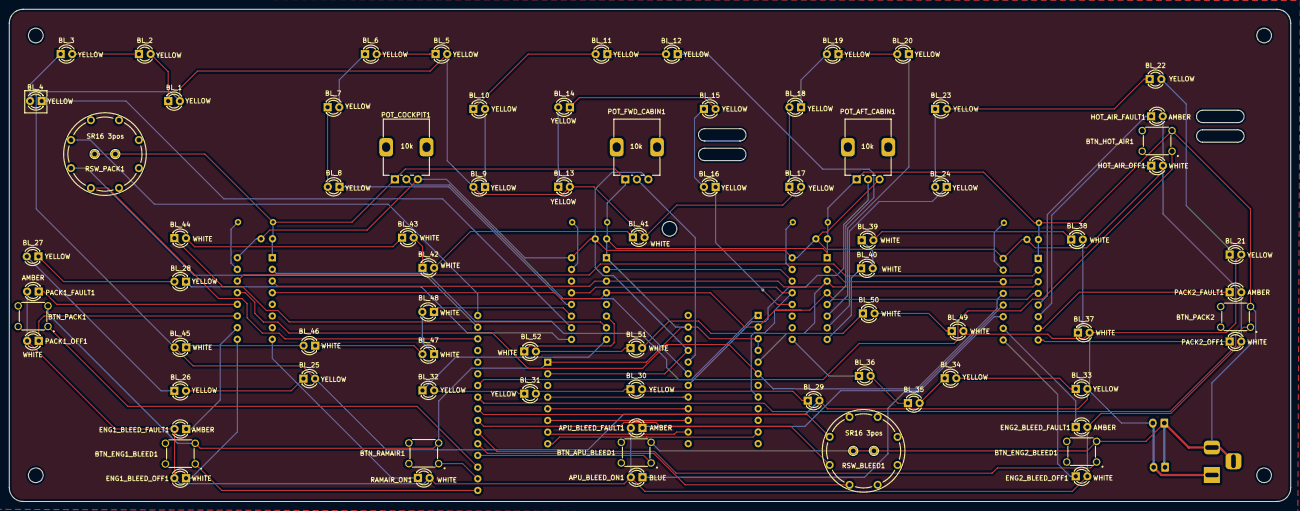
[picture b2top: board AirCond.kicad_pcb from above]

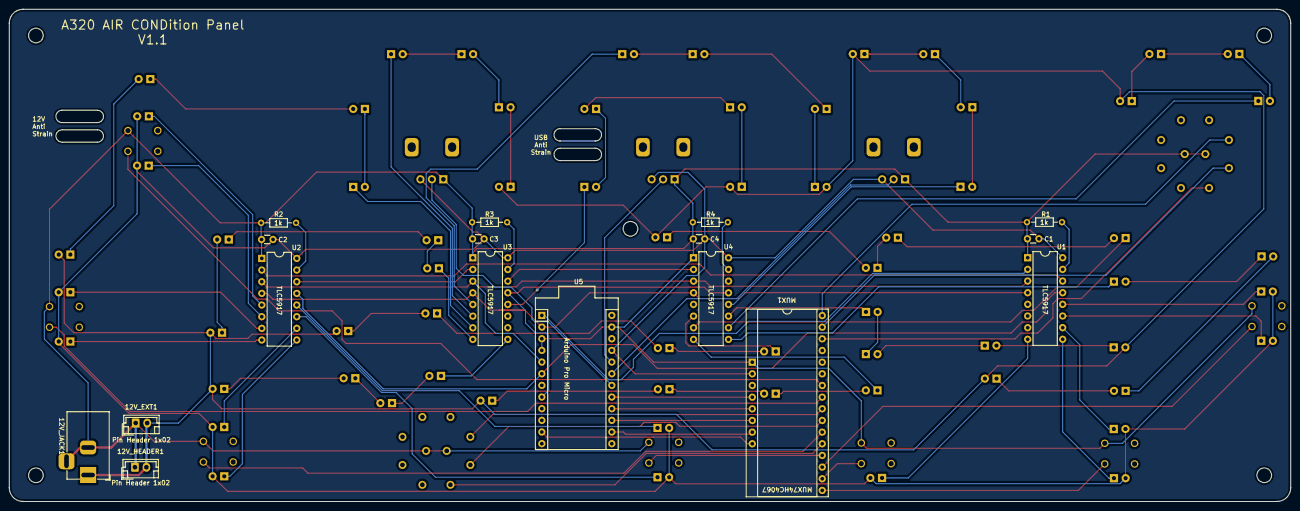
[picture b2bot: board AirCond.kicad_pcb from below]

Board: 2 copper layers, 279.2 x 107.2 mm, 94 parts (17 on the bottom side), 101 nets.

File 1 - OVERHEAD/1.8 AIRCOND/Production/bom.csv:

Designator,Footprint,Quantity,Value,LCSC Part #
"12V_EXT1, 12V_HEADER1",JST_EH_B2B-EH-A_1x02_P2.50mm_Vertical,2,Pin Header 1x02,
12V_JACK1,BarrelJack_Horizontal,1,Power Jack,
"APU_BLEED_FAULT1, ENG1_BLEED_FAULT1, ENG2_BLEED_FAULT1, HOT_AIR_FAULT1, PACK1_FAULT1, PACK2_FAULT1",LED_D3.0mm,6,AMBER,
APU_BLEED_ON1,LED_D3.0mm,1,BLUE,
"BL_1, BL_10, BL_11, BL_12, BL_13, BL_14, BL_15, BL_16, BL_17, BL_18, BL_19, BL_2, BL_20, BL_21, BL_22, BL_23, BL_24, BL_25, BL_26, BL_27, BL_28, BL_29, BL_3, BL_30, BL_31, BL_32, BL_33, BL_34, BL_35, BL_36, BL_4, BL_5, BL_6, BL_7, BL_8, BL_9",LED_D3.0mm,36,YELLOW,
"BL_37, BL_38, BL_39, BL_40, BL_41, BL_42, BL_43, BL_44, BL_45, BL_46, BL_47, BL_48, BL_49, BL_50, BL_51, BL_52, ENG1_BLEED_OFF1, ENG2_BLEED_OFF1, HOT_AIR_OFF1, PACK1_OFF1, PACK2_OFF1, RAMAIR_ON1",LED_D3.0mm,22,WHITE,
"BTN_APU_BLEED1, BTN_ENG1_BLEED1, BTN_ENG2_BLEED1, BTN_HOT_AIR1, BTN_PACK1, BTN_PACK2, BTN_RAMAIR1",B3F1000,7,B3F-1055,
"C1, C2, C3, C4",C_Disc_D3.0mm_W1.6mm_P2.50mm,4,0.1uF Ceramic,
MUX1,MUX74HC4067,1,MUX74HC4067,
"POT_AFT_CABIN1, POT_COCKPIT1, POT_FWD_CABIN1",Potentiometer_Alps_RK09K_Single_Vertical,3,10k,
"R1, R2, R3, R4",R_Axial_DIN0204_L3.6mm_D1.6mm_P7.62mm_Horizontal,4,1k,
"RSW_BLEED1, RSW_PACK1",SR16-AB,2,SR16 3pos,
"U1, U2, U3, U4",DIP-16_W7.62mm,4,TLC5917,
U5,Sparkfun_Pro_Micro,1,Arduino Pro Micro,
